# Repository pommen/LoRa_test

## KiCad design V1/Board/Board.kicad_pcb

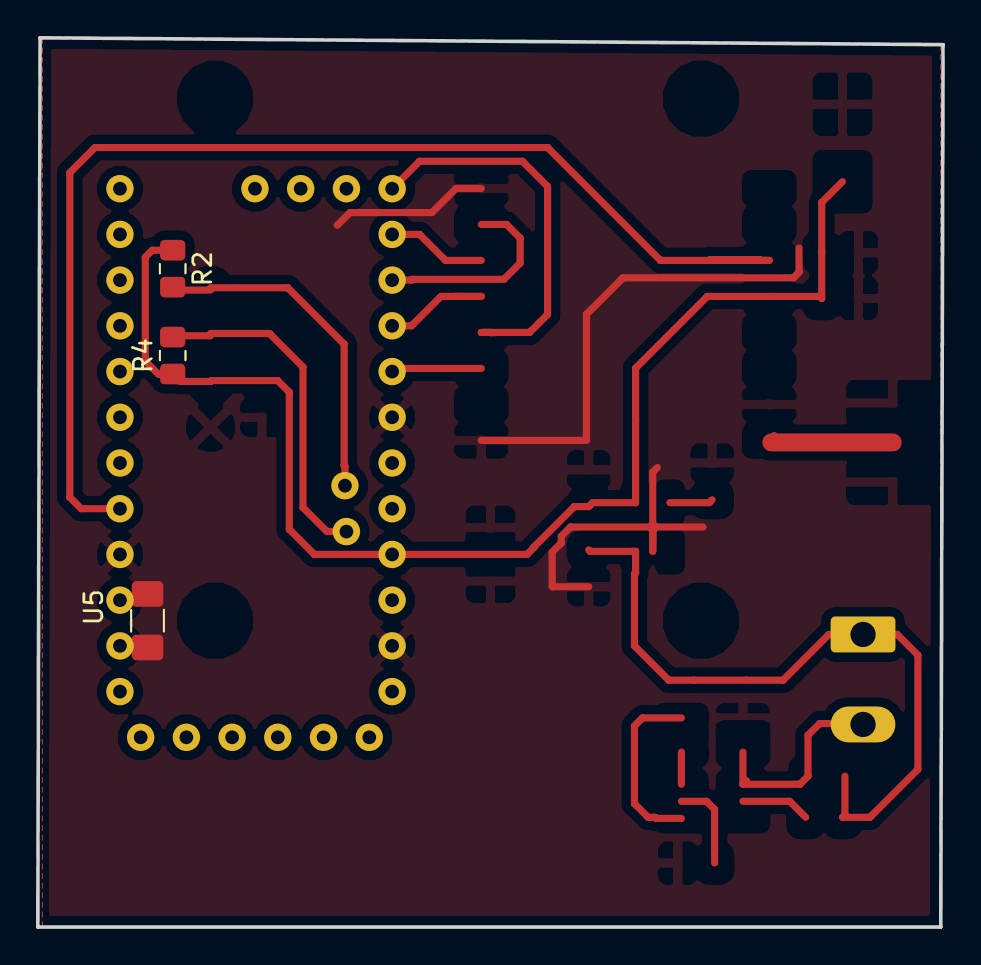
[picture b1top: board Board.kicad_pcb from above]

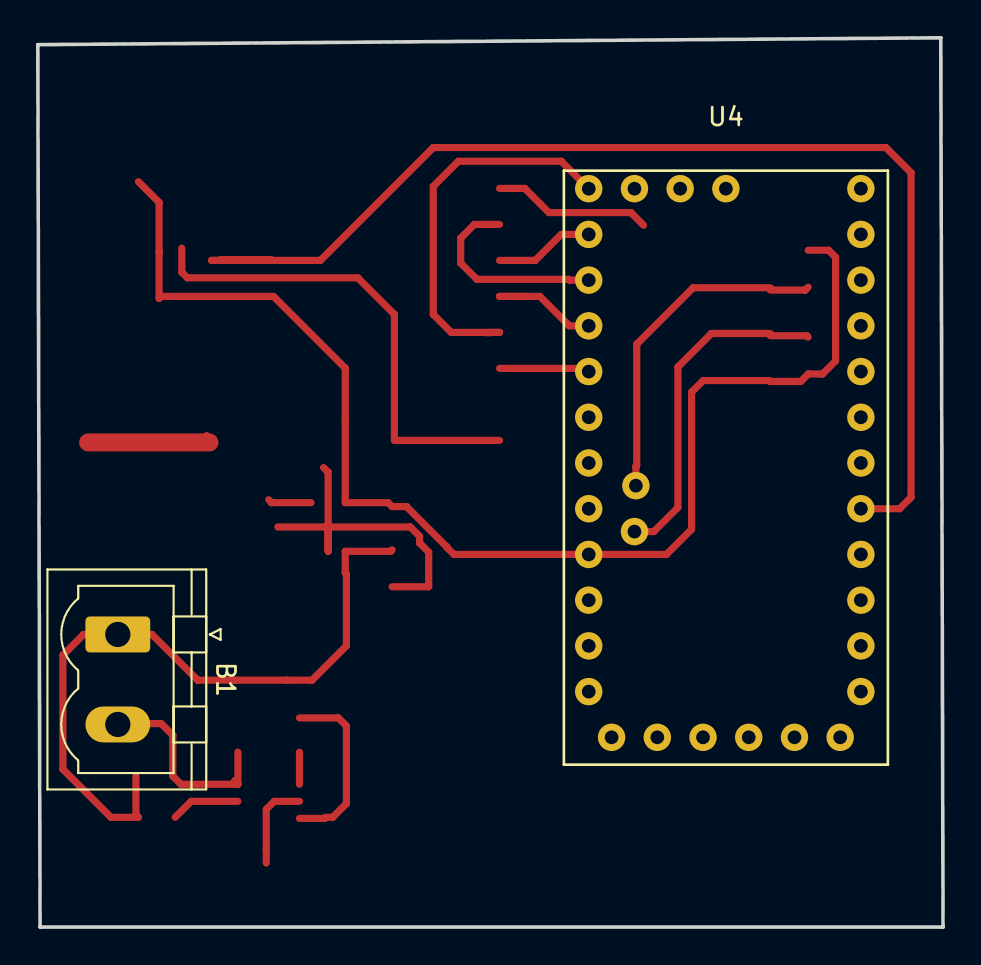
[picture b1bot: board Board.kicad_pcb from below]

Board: 2 copper layers, 50.3 x 49.4 mm, 5 parts (2 on the bottom side), 4 nets.

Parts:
B1: 18650_Holder; PhoenixContact_MSTBVA_2,5_2-G_1x02_P5.00mm_Vertical
R2, R4: 4k7; R_0805_2012Metric_Pad1.15x1.40mm_HandSolder
U4: pro-mini-deek; Pro-mini-deek
U5: OLED_128x64_i2c_0.96; libOLED_128x64_i2c

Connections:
+3V3: R2.1, R4.1, U4.23
GND: U4.4, U4.18, U4.25, U5.1, U5.2
scl: R4.2, U4.22
sda: R2.2, U4.21

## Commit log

2018-10-06 done
